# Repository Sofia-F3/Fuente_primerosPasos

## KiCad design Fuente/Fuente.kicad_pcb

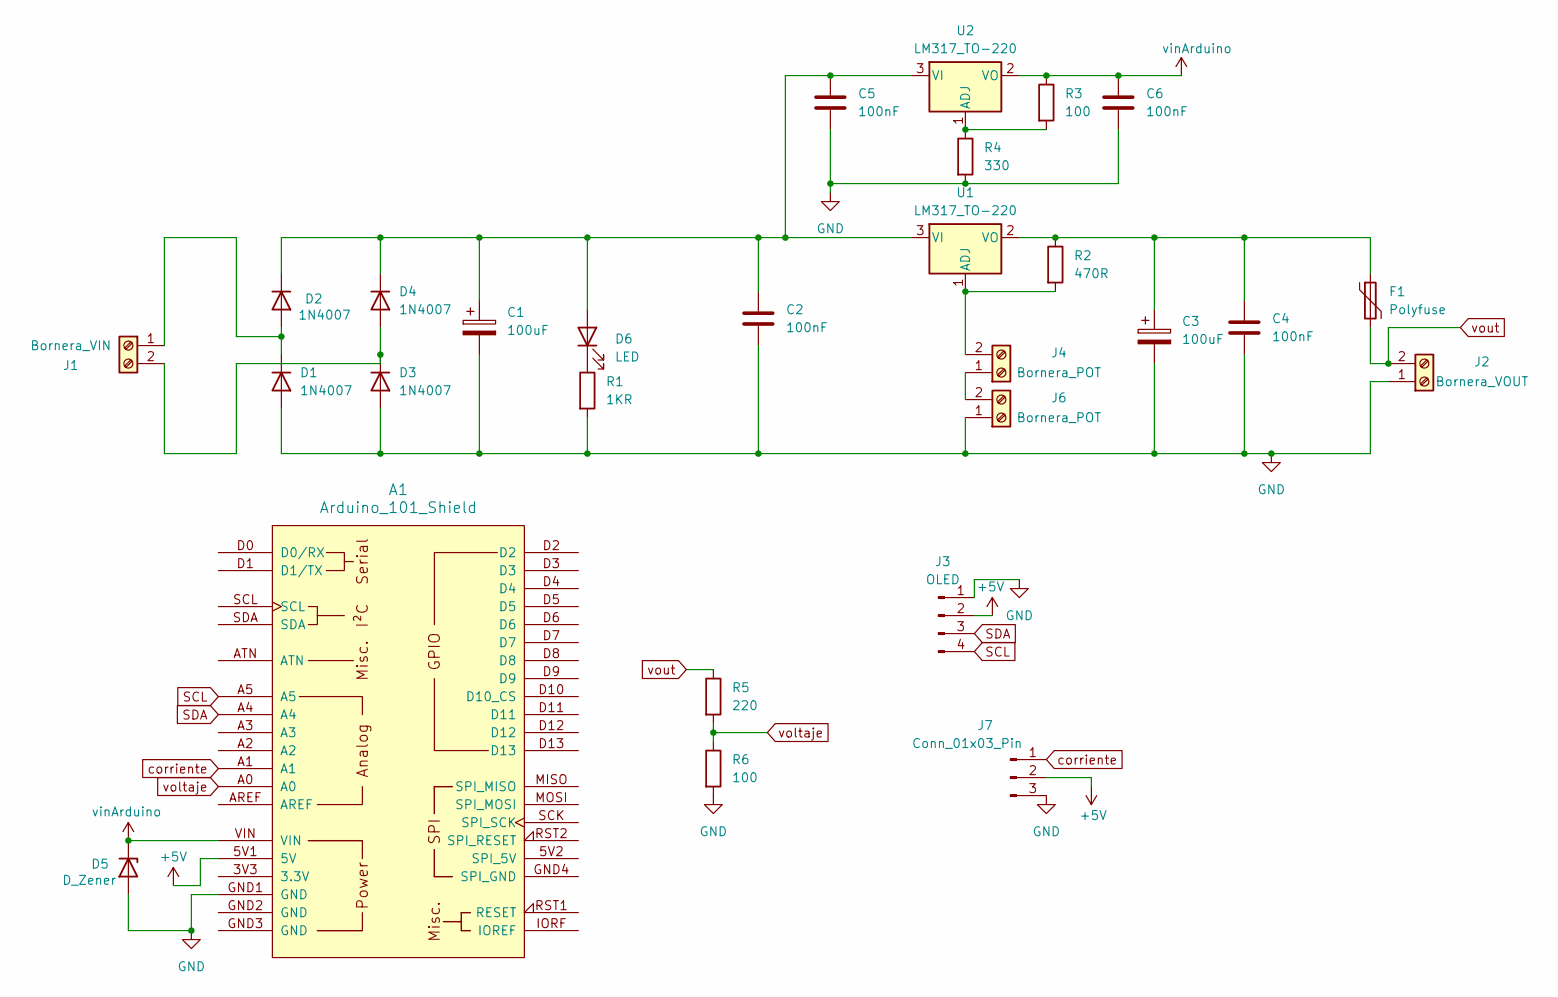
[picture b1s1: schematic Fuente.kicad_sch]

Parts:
A1: Arduino_101_Shield
C1, C3: 100uF; CP_Radial_D6.3mm_P2.50mm
C2, C4, C5, C6: 100nF; C_Disc_D5.0mm_W2.5mm_P5.00mm
D1, D2, D3, D4: 1N4007; D_DO-41_SOD81_P10.16mm_Horizontal
D5: D_Zener; D_A-405_P10.16mm_Horizontal
D6: LED; LED_D5.0mm
F1: Polyfuse; C_Disc_D5.0mm_W2.5mm_P5.00mm
J1: Bornera_VIN; TerminalBlock_MaiXu_MX126-5.0-02P_1x02_P5.00mm
J2: Bornera_VOUT; TerminalBlock_MaiXu_MX126-5.0-02P_1x02_P5.00mm
J3: OLED; PinHeader_1x04_P2.54mm_Horizontal
J4, J6: Bornera_POT; PinHeader_1x02_P2.54mm_Horizontal
J7: Conn_01x03_Pin; PinHeader_1x03_P2.54mm_Horizontal
R1: 1KR; R_Axial_DIN0207_L6.3mm_D2.5mm_P7.62mm_Horizontal
R2: 470R; R_Axial_DIN0207_L6.3mm_D2.5mm_P7.62mm_Horizontal
R3, R6: 100; R_Axial_DIN0207_L6.3mm_D2.5mm_P7.62mm_Horizontal
R4: 330; R_Axial_DIN0207_L6.3mm_D2.5mm_P7.62mm_Horizontal
R5: 220; R_Axial_DIN0207_L6.3mm_D2.5mm_P7.62mm_Horizontal
U1, U2: LM317_TO-220; TO-220-3_Vertical

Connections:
+5V: A1.5V1 (5V), J3.2, J7.2
GND: A1.GND1 (GND), C1.2, C2.2, C3.2, C4.2, C5.2, C6.2, D1.2 (A), D3.2 (A), D5.2 (A), J2.1, J3.1, J6.1, J7.3, R1.2, R4.2, R6.2
unnamed: D1.1 (K), D2.2 (A), J1.1
unnamed: C1.1, C2.1, C5.1, D2.1 (K), D4.1 (K), D6.2 (A), U1.3 (VI), U2.3 (VI)
unnamed: D3.1 (K), D4.2 (A), J1.2
unnamed: D6.1 (K), R1.1
unnamed: J4.1, J6.2
unnamed: J4.2, R2.2, U1.1 (ADJ)
unnamed: C3.1, C4.1, F1.1, R2.1, U1.2 (VO)
unnamed: R3.2, R4.1, U2.1 (ADJ)
SCL: A1.A5, J3.4
SDA: A1.A4, J3.3
corriente: A1.A1, J7.1
vinArduino: A1.VIN, C6.1, D5.1 (K), R3.1, U2.2 (VO)
voltaje: A1.A0, R5.2, R6.1
vout: F1.2, J2.2, R5.1

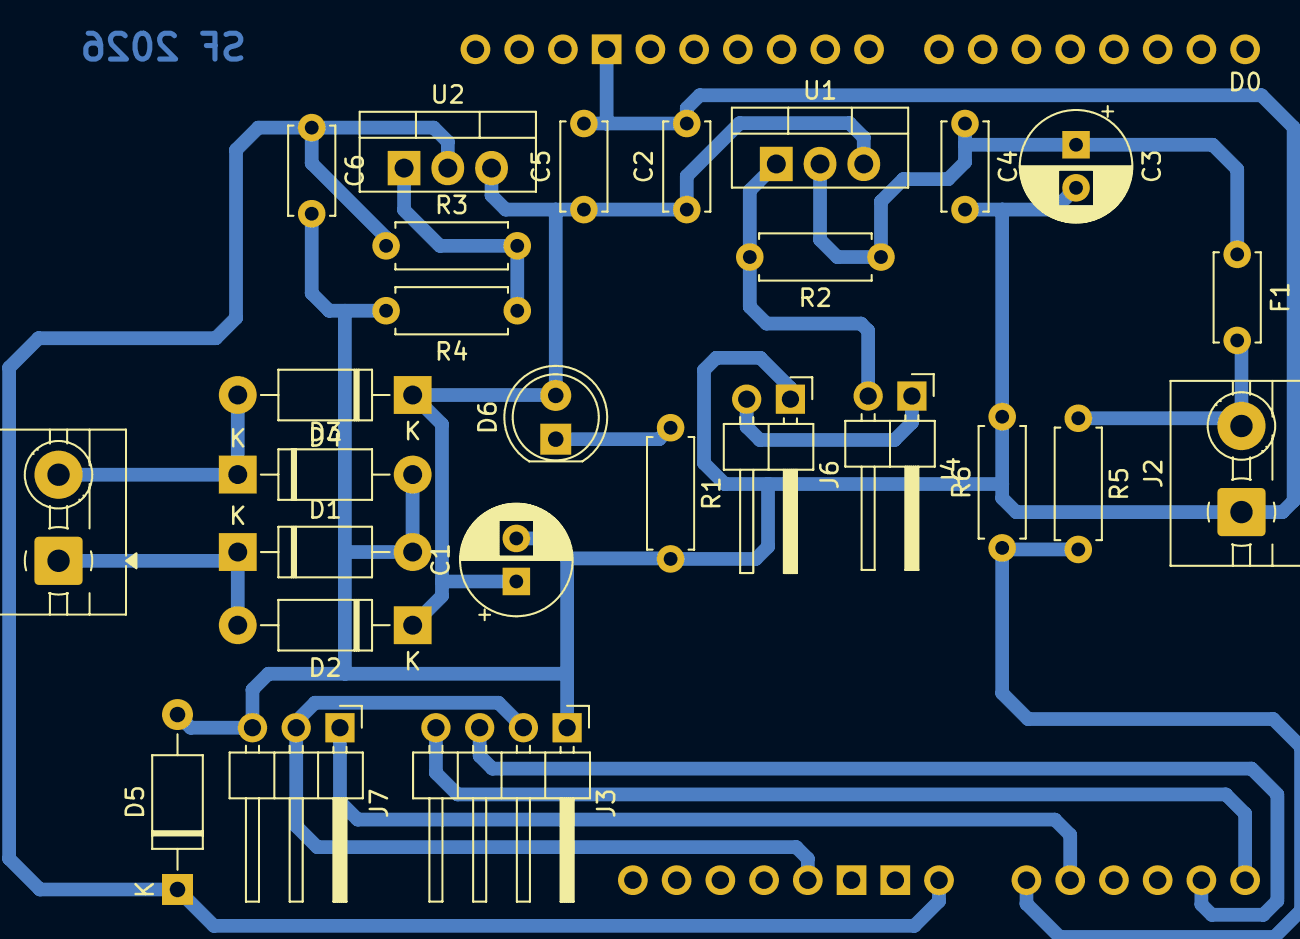
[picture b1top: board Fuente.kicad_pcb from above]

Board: 2 copper layers, 28 parts (0 on the bottom side), 16 nets.

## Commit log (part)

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2026-02-01 pcb terminada
